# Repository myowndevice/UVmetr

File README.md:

## Измеритель УФ-индекса и температуры

Собрались на море? Возьмите с собой этот прибор!
С его помощью вы будете загорать правильно — точное измерение мгновенного и накопленного индекса ультра фиолетового излучения. Вы будете знать прогрелось ли море — точное измерение температуры воды, с помощью термопары К типа.  Насколько жарко на улице — измерение температуры воздуха.  Также он пригодится вам на даче — правильное приготовление шашлыка. Миниатюрный размер 35х45х18, встроенный аккумулятор, а также масса других полезных функций.
Ключевые параметры измерителя УФ-индекса и температуры:
- Компактный размер
- Питание от аккумулятора, длительная работа от одного заряда
- Измерения индекса УФ излучения в двух диапазонах UVA и UVB
- Измерение температуры с помощью термопары К типа, подключение ее через разъем
- Измерение температуры воздуха
- Индикация измеренных данных — миниатюрный ЖК (на солнце он читается лучше других индикаторов) дисплей
- Возможность индикации звуком о различных событиях
- Широкий набор функций и возможность доработки.
- Микроконтроллерное управление на базе STM8.
- Наличие разъёма для расширения функций.

Данный репозитарий содержит все необходимые файлы для платы управления моторами.Если вы будете скачивать файлы через web не забудьте скачать общую папку Kicadlib.

Ознакомится со схемой и подробным описанием данного прибора, программы, и порядка сборки можно, [прочитав эту подробную статью](http://myowndevice.ru/index.php/pribory/item/46-izmeritel-uf-indeksa-i-temperatury)

Также [здесь](http://myowndevice.ru) вы найдете подробное описание как сделать другие приборы, много теории о том, как их делать, методику изготовления печатных плат и много другого.

Изучай микроконтроллеры, разрабатывай и делай электронику дома сам!

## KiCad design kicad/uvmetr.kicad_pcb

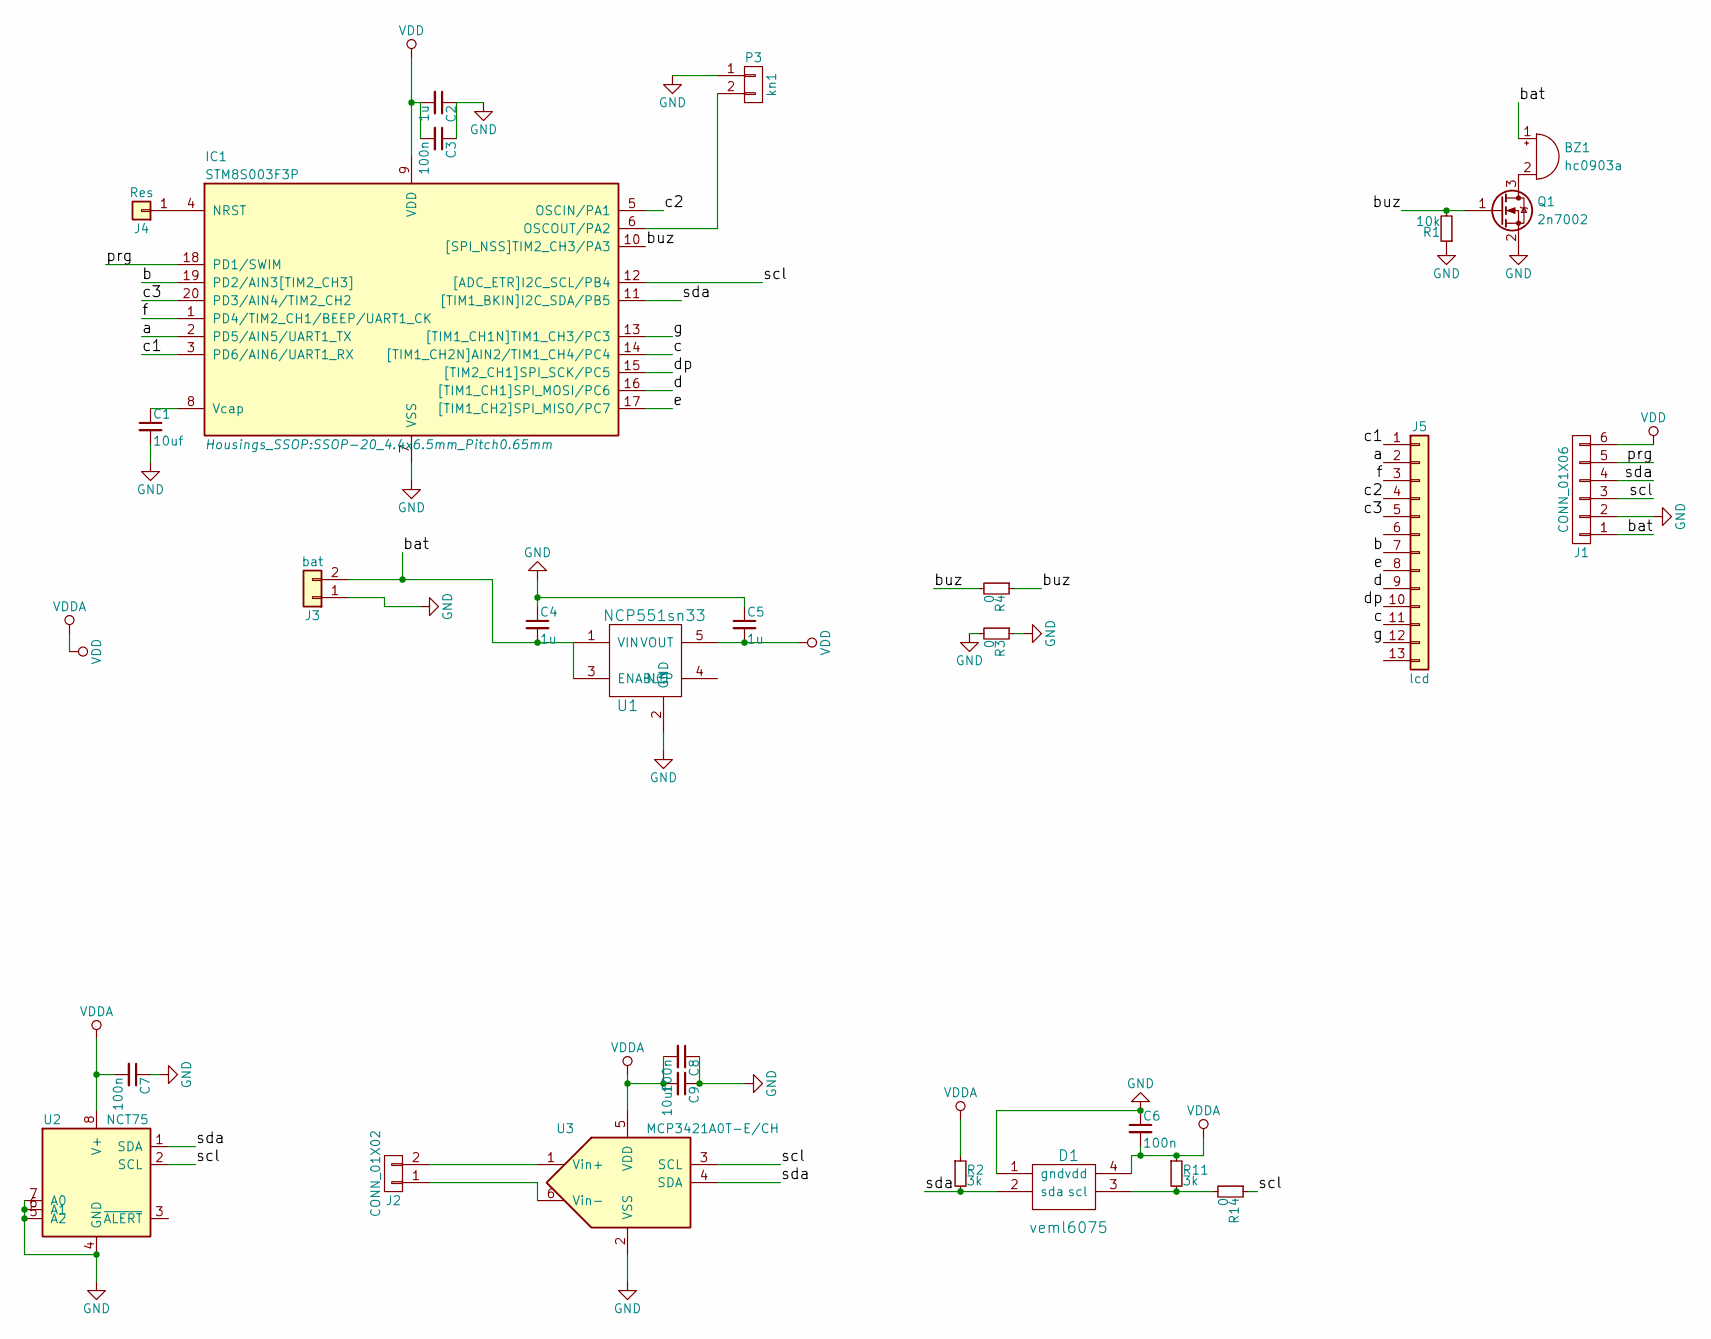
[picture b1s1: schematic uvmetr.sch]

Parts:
BZ1: hc0903a
C1, C9: 10uf; C_0805_HandSoldering
C2, C4, C5: 1u; C_0805_HandSoldering
C3, C6, C7, C8: 100n; C_0603_HandSoldering
D1: veml6075
IC1: STM8S003F3P; SSOP-20_4.4x6.5mm_Pitch0.65mm
J1: CONN_01X06; Pin_Header_Angled_1x06_Pitch2.54mm
J2: CONN_01X02; Pin_Header_Angled_1x02_Pitch2.54mm
J3: bat; Pin_Header_Angled_1x02_Pitch2.54mm
J4: Res; wirepad_mini
J5: lcd; PIN13_Pitch1_5_lcd
P3: kn1; SW_PUSH_6mm
Q1: 2n7002; SOT-23
R1: 10k; R_0603_HandSoldering
R2, R11: 3k; R_0603_HandSoldering
R3, R4, R14: 0; R_0603_HandSoldering
U1: NCP551sn33; SOT-23-5_HandSoldering
U2: NCT75; SSOP-8_2.95x2.8mm_Pitch0.65mm
U3: MCP3421A0T-E/CH; SOT-23-6_Handsoldering

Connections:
/a: IC1.2 (PD5/AIN5/UART1_TX), J5.2
/b: IC1.19 (PD2/AIN3[TIM2_CH3]), J5.7
/bat: BZ1.1 (-), C4.2, J1.1, J3.2, U1.1 (VIN), U1.3 (ENABLE)
/buz: IC1.10 ([SPI_NSS]TIM2_CH3/PA3), Q1.1 (G), R1.2, R4.1, R4.2
/c: IC1.14 ([TIM1_CH2N]AIN2/TIM1_CH4/PC4), J5.11
/c1: IC1.3 (PD6/AIN6/UART1_RX), J5.1
/c2: IC1.5 (OSCIN/PA1), J5.4
/c3: IC1.20 (PD3/AIN4/TIM2_CH2), J5.5
/d: IC1.16 ([TIM1_CH1]SPI_MOSI/PC6), J5.9
/dp: IC1.15 ([TIM2_CH1]SPI_SCK/PC5), J5.10
/e: IC1.17 ([TIM1_CH2]SPI_MISO/PC7), J5.8
/f: IC1.1 (PD4/TIM2_CH1/BEEP/UART1_CK), J5.3
/g: IC1.13 ([TIM1_CH1N]TIM1_CH3/PC3), J5.12
/prg: IC1.18 (PD1/SWIM), J1.5
/scl: IC1.12 ([ADC_ETR]I2C_SCL/PB4), J1.3, R14.1, U2.2 (SCL), U3.3 (SCL)
/sda: D1.2 (sda), IC1.11 ([TIM1_BKIN]I2C_SDA/PB5), J1.4, R2.2, U2.1 (SDA), U3.4 (SDA)
GND: C1.2, C2.1, C3.1, C4.1, C5.1, C6.1, C7.1, C8.1, C9.1, D1.1 (gnd), IC1.7 (VSS), J1.2, J3.1, P3.1, Q1.2 (S), R1.1, R3.1, R3.2, U1.2 (GND), U2.4 (GND), U2.5 (A2), U2.6 (A1), U2.7 (A0), U3.2 (VSS)
unnamed: BZ1.2 (+), Q1.3 (D)
unnamed: C1.1, IC1.8 (Vcap)
unnamed: D1.3 (scl), R11.2, R14.2
unnamed: IC1.4 (NRST), J4.1
unnamed: IC1.6 (OSCOUT/PA2), P3.2
unnamed: J2.1, U3.6 (Vin-)
unnamed: J2.2, U3.1 (Vin+)
VDD: C2.2, C3.2, C5.2, C6.2, C7.2, C8.2, C9.2, D1.4 (vdd), IC1.9 (VDD), J1.6, R2.1, R11.1, U1.5 (VOUT), U2.8 (V+), U3.5 (VDD)

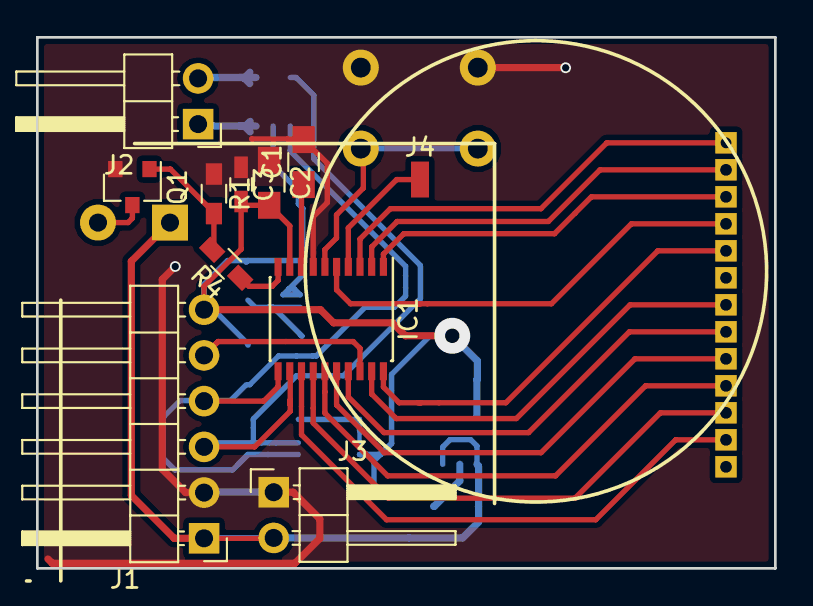
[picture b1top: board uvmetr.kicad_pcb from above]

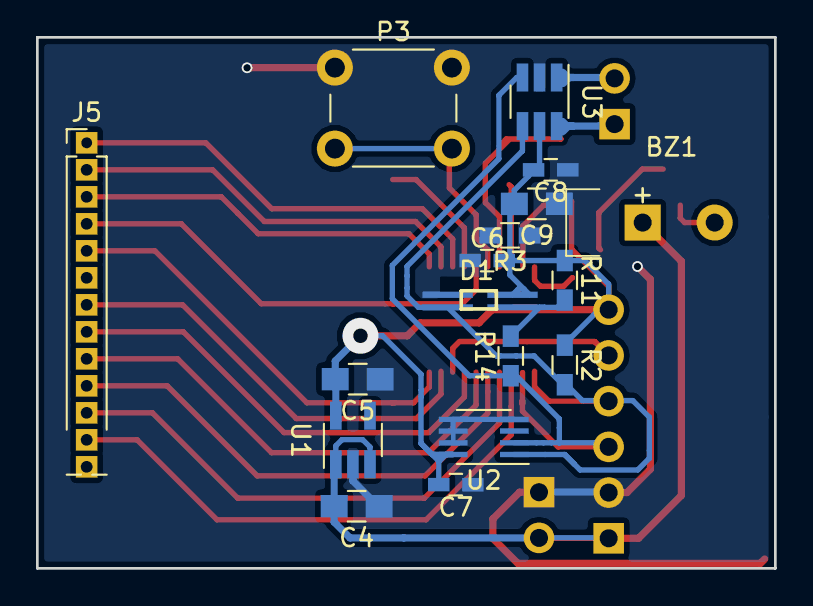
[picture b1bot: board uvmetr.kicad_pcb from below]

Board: 2 copper layers, 41.0 x 29.5 mm, 28 parts (17 on the bottom side), 25 nets.

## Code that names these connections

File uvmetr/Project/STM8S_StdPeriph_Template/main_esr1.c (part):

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	readytosleep = 1;
	//Delay(10);
	
	//off disp! need pullup PA1 !
	GPIO_Init(GPIOD,ALL_PORTD,GPIO_MODE_IN_PU_NO_IT);
	GPIO_Init(GPIOA,ALL_PORTA,GPIO_MODE_IN_PU_NO_IT);
	GPIO_Init(GPIOC,ALL_PORTC,GPIO_MODE_IN_PU_NO_IT);	
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*/

void calclcd(void) {
	//com0 - 3 pd6
	//com1 - 2 pd5
	//com2 - 17 pc7
	//com3 - 16 pc6
	
	//5 - 1  pd4  0
	//7 - 15 pc5  1
	//8 - 14 pc4  2
	//9 - 13 pc3  3
	//10 - 5 pa1  4
	//11 - 20 pd3 5
	//12 - 19 pd2 6
	u8 i,j;
	
	if (timeshowrezhim) {
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
/*
void calclcd_old(void) {
	//com0 - 3 pd6
	//com1 - 2 pd5
	//com2 - 17 pc7
	//com3 - 16 pc6
	
	//5 - 1  pd4  0
	//7 - 15 pc5  1
	//8 - 14 pc4  2
	//9 - 13 pc3  3
	//10 - 5 pa1  4
	//11 - 20 pd3 5
	//12 - 19 pd2 6
	u8 i;
	
	blockcopylcd=1;
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
  I2C_Init(I2C_MAX_STANDARD_FREQ, (uint8_t)0xA0, I2C_DUTYCYCLE_2, I2C_ACK_CURR, I2C_ADDMODE_7BIT, 7);

	//com0 - 3 pd6
	//com1 - 2 pd5
	//com2 - 17 pc7
	//com3 - 16 pc6
	
	//5 - 1  pd4  5
	//7 - 15 pc5  6
	//8 - 14 pc4  7
	//9 - 13 pc3  8
	//10 - 5 pa1  9
	//11 - 20 pd3 10
	//12 - 19 pd2 11
	for (i=0;i<12;i++) {
		lcdpins[i].porta = 0;
		lcdpins[i].portd = 0;
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
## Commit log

2019-02-16 start

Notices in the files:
uvmetr/Project/STM8S_StdPeriph_Template/main_esr1.c:
© COPYRIGHT 2014 STMicroelectronics
Licensed under MCD-ST Liberty SW License Agreement V2, (the "License");
(C) COPYRIGHT STMicroelectronics *****END OF FILE
